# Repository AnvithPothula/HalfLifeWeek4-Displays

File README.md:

# HalfLifeWeek4-Displays
For Week 4 I designed my own project from scratch: a Wi-Fi desk dashboard. It's a small PCB with an ESP32-S3-Zero, a 2.0" color screen, and one rotary encoder. It sits on my desk and shows the things I check every day, so I don't have to pick up my phone for them. Turning the knob switches between 9 pages, and pressing it does something different on each page.
 
**3D Model / Final PCB Render:**

**Schematic:**

**Board Layout & Routing:**
 
Combined Layout:

Front Copper Layer:

Back Copper Layer:

**What it is and how it works:**
 
The dashboard has 9 pages:

- Clock
- Weather
- Pomodoro timer
- Daily chess puzzle from lichess
- My lichess and chess.com ratings
- My FRC team's (team 2220) next event and how many days until it starts
- GitHub stuff
- Quote/fun fact
- Countdowns (days until dates I care about)
 
These are the parts:
 
* **Waveshare ESP32-S3-Zero:** This is kind of like the brain of the board. It also connects to Wi-Fi, downloads data from APIs, and draws everything on the screen.
* **Screen:** This uses SPI to "talk" to the ESP32. It plugs into the PCB.
* **AO3401A and resistor:** This switches the screen's backlight. The ESP32 sends a PWM signal to it, which lets the firmware dim the screen for night mode. The resistor keeps the backlight off while the ESP32 is starting up.
* **Encoder:** Turning it changes the page, and if you do a short press it does an action (depending on the page). If you do a long press, it will either reset the timer or toggle night mode.
* **Capacitor:** This is placed next to the screen connector to smooth out the screen's power.
* **The ESP32-S3-Zero's built in LED:** This changes color to match the current page, and turns red/green when the Pomodoro timer is running.
 
**Why I made it:**
 
In Weeks 1 to 3 I followed guides and then changed them. However, for this week, I wanted to design the whole thing myself. I also wanted something I would actually use every day. Since I play chess a lot, I'm on an FRC team, and I use Pomodoro timers to study, I decided to put all of those on one screen, since this week is about displays. I also learned a lot from making this, especially on the software side (since most of the hardware stuff was similar to Weeks 1 and 3).
 
**How to assemble and flash the firmware:**
 
**1. How to assemble the board**
 
You need a soldering iron, solder, flux, tweezers, flush cutters, and a multimeter. You also want to solder from the flattest part to the tallest part:
 
1. **Q1 (AO3401A MOSFET):** Put a little solder on one pad, hold the part with tweezers, and melt that pad to tack it down. Check that all 3 legs line up, then solder the other 2.
2. **C1 (10uF capacitor):** Do the same thing that you did for Q1: tack one end, then solder the other.
3. **U1 (ESP32-S3-Zero):** Line it up with the outline, with the USB-C port over the board edge. Tack one corner, then solder every edge pad and check for bridges.
4. **R1 (10k resistor):** Bend the legs, push it through, solder and trim.
5. **SW1 (EC11 encoder):** Snap it in, then solder the 5 pins and the 2 big mounting tabs.
6. **J1 (screen):** Push the screen's header pins through the 8 holes, with GND in the square pad. Screw the screen to the 4 mounting holes with M2 screws (optional), then solder the pins.

Before plugging in, use the multimeter in continuity mode to check that 3V3 and GND are not shorted.
 
**2. How to flash the firmware**
 
1. Install the Arduino IDE.
2. In the Boards Manager, install esp32 by Espressif Systems and select ESP32S3 Dev Modules as the board.
3. Under the Tools menu, set USB CDC On Boot to Enabled so the Serial Monitor works over USB-C.
4. Install these libraries in the Library Manager:
   * Adafruit ST7735 and ST7789 Library
   * Adafruit GFX
   * ArduinoJson
   * Adafruit NeoPixel
5. Copy DeskDashboard/secrets_example.h to DeskDashboard/secrets.h and fill in your Wi-Fi name, Wi-Fi password, and (optionally) a free read API key from The Blue Alliance.
6. At the top of DeskDashboard.ino, change the usernames, location, and countdown dates to your own.
7. Open DeskDashboard/DeskDashboard.ino, plug the board in with a USB-C data cable, and click Upload. If it doesn't upload, hold the BOOT button on the ESP32-S3-Zero, tap RESET, release BOOT, and try again.
The screen should show "Connecting to Wi-Fi...". Turn the knob to check that the pages and LED color change.
 
**BOM:**
 
The full bill of materials is in [BOM.csv](BOM.csv):
 
| Item | Qty | Supplier | Cost/item | Total cost | Link |
| --- | ---: | --- | ---: | ---: | --- |
| ESP32-S3-Zero (no headers) | 1 | AliExpress | $4.32 | $4.32 | [AliExpress](https://www.aliexpress.us/item/3256807949476561.html) |
| 2.0" IPS ST7789 screen (8-pin) | 1 | AliExpress | $6.18 | $6.18 | [AliExpress](https://www.aliexpress.us/item/3256804844327418.html) |
| AO3401A MOSFET (100-pack) | 1 | AliExpress | $1.84 | $1.84 | [AliExpress](https://www.aliexpress.us/item/2251801213228611.html) |
| 10uF 0805 capacitor (200-pack) | 1 | AliExpress | $2.26 | $2.26 | [AliExpress](https://www.aliexpress.us/item/2251800929439420.html) |
| EC11 rotary encoder (spare from Week 3) | 1 | AliExpress | $0.00 | $0.00 | [AliExpress](https://www.aliexpress.us/item/3256808530463909.html) |
| 10k resistor (spare from Week 1) | 1 | AliExpress | $0.00 | $0.00 | [AliExpress](https://www.aliexpress.us/item/3256806338200607.html) |
| PCB (2-layer, 95x70mm) | 1 | JLCPCB | $4.00 | $4.00 | [JLCPCB](https://jlcpcb.com/) |
| Shipping (AliExpress Choice) | — | AliExpress | — | $0.00 | — |
| Shipping (JLCPCB Global Standard Direct Line) | — | JLCPCB | — | $8.16 | — |
| Estimated sales tax (8.125% on AliExpress parts) | — | — | — | $1.19 | — |
| **Estimated total** |  |  |  | **$27.95** |  |

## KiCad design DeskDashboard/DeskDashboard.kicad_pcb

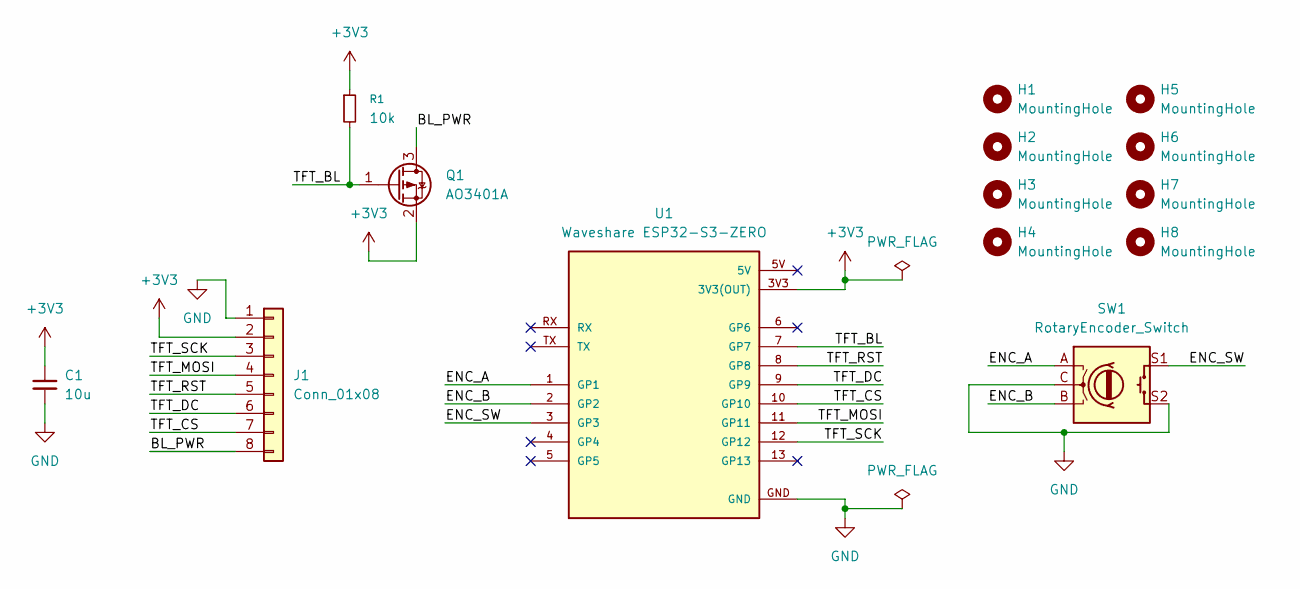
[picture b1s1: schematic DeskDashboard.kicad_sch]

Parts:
C1: 10u; C_0805_2012Metric
H1, H2, H3, H4: MountingHole; MountingHole_2.7mm_M2.5
H5, H6, H7, H8: MountingHole; MountingHole_3.2mm_M3
J1: Conn_01x08; PinHeader_1x08_P2.54mm_Vertical
Q1: AO3401A; SOT-23
R1: 10k; R_Axial_DIN0207_L6.3mm_D2.5mm_P10.16mm_Horizontal
SW1: RotaryEncoder_Switch; RotaryEncoder_Alps_EC11E-Switch_Vertical_H20mm
U1: Waveshare ESP32-S3-ZERO; Waveshare ESP32-S3-Zero; PARTREV NA

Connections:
+3V3: C1.1, J1.2, Q1.2 (S), R1.1, U1.3V3 (3V3(OUT))
/BL_PWR: J1.8, Q1.3 (D)
/ENC_A: SW1.A, U1.1 (GP1)
/ENC_B: SW1.B, U1.2 (GP2)
/ENC_SW: SW1.S1, U1.3 (GP3)
/TFT_BL: Q1.1 (G), R1.2, U1.7 (GP7)
/TFT_CS: J1.7, U1.10 (GP10)
/TFT_DC: J1.6, U1.9 (GP9)
/TFT_MOSI: J1.4, U1.11 (GP11)
/TFT_RST: J1.5, U1.8 (GP8)
/TFT_SCK: J1.3, U1.12 (GP12)
GND: C1.2, J1.1, SW1.C, SW1.S2, U1.GND

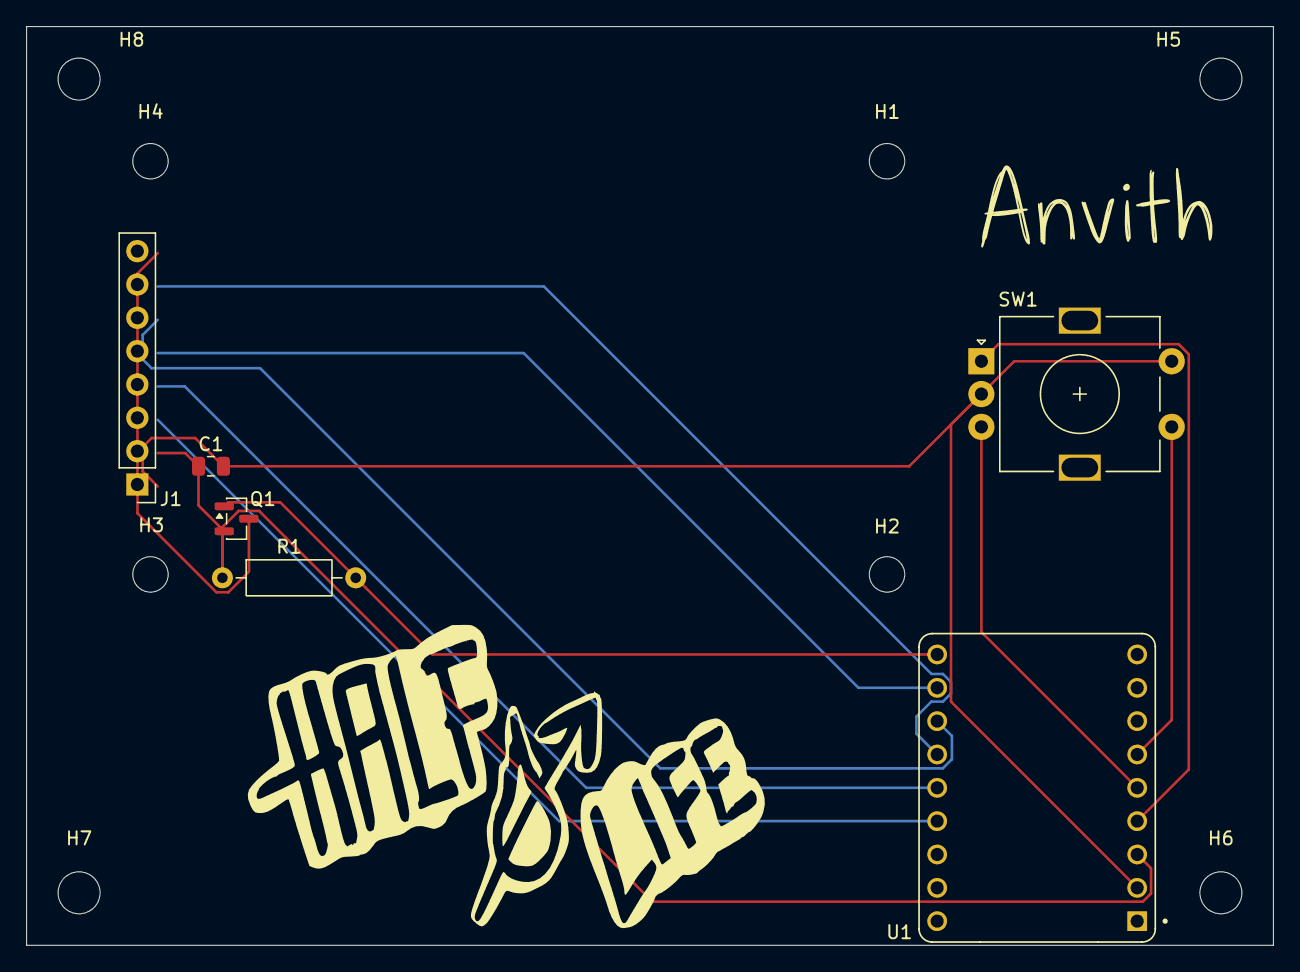
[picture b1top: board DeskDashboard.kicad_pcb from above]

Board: 2 copper layers, 95.0 x 70.0 mm, 14 parts (0 on the bottom side), 12 nets.

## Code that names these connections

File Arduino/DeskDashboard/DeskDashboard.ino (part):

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const int BRIGHT_NIGHT = 25;

// pins
#define TFT_SCK 12
#define TFT_MOSI 11
#define TFT_CS 10
#define TFT_DC 9
#define TFT_RST 8
#define TFT_BL 7
#define ENC_A 1
#define ENC_B 2
#define ENC_SW 3
#define LED_PIN 21

Adafruit_ST7789 tft = Adafruit_ST7789(TFT_CS, TFT_DC, TFT_RST);
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  ledcAttach(TFT_BL, 5000, 8);
  setBrightness(0);

  pinMode(ENC_A, INPUT_PULLUP);
  pinMode(ENC_B, INPUT_PULLUP);
  pinMode(ENC_SW, INPUT_PULLUP);
  encoderState = (digitalRead(ENC_A) << 1) | digitalRead(ENC_B);
  attachInterrupt(digitalPinToInterrupt(ENC_A), onEncoderChange, CHANGE);
  attachInterrupt(digitalPinToInterrupt(ENC_B), onEncoderChange, CHANGE);

  if (USE_STATUS_LED) {
    statusLed.begin();
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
